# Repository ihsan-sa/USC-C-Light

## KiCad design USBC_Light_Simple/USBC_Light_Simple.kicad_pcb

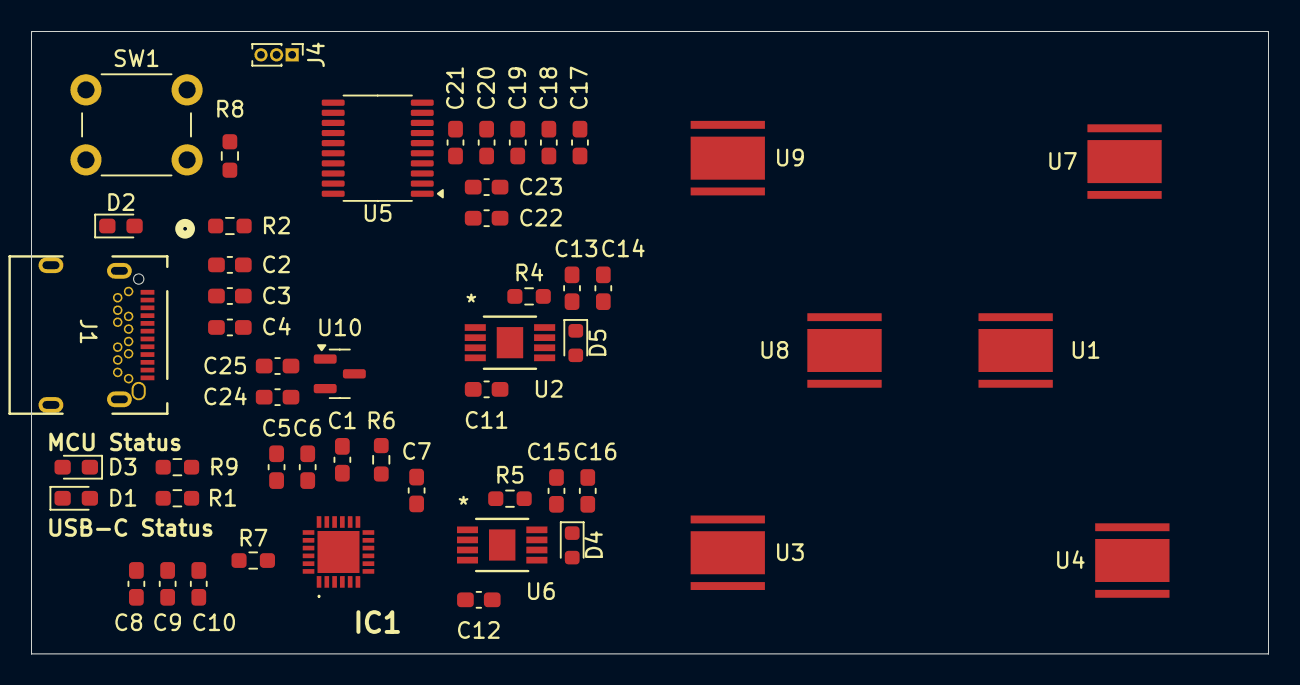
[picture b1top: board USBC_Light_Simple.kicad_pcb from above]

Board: 2 copper layers, 79.5 x 40.0 mm, 52 parts (0 on the bottom side), 36 nets, no tracks yet.

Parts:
C1, C4, C6, C7, C10, C11, C12, C13, C15, C19, C20, C25: 100n; C_0603_1608Metric_Pad1.08x0.95mm_HandSolder
C2, C8: 10u; C_0603_1608Metric_Pad1.08x0.95mm_HandSolder
C3, C5, C9, C14, C16, C17, C18, C24: 1u; C_0603_1608Metric_Pad1.08x0.95mm_HandSolder
C21: 10n; C_0603_1608Metric_Pad1.08x0.95mm_HandSolder
C22, C23: *; C_0603_1608Metric_Pad1.08x0.95mm_HandSolder
D1, D2, D3: LED; LED_0603_1608Metric_Pad1.05x0.95mm_HandSolder
D4, D5: D; D_0603_1608Metric
IC1: AP33772SDKZ-13-FA01; AP33772SDKZ13FA01
J1: USB_C_Receptacle; CONN24_4056-03-A_GCT
J4: Screw_Terminal_01x03; PinHeader_1x03_P1.00mm_Vertical
R1, R9: 1k; R_0603_1608Metric_Pad0.98x0.95mm_HandSolder
R2: 100k; R_0603_1608Metric_Pad0.98x0.95mm_HandSolder
R4, R5: RS; R_0603_1608Metric_Pad0.98x0.95mm_HandSolder
R6, R8: 10k; R_0603_1608Metric_Pad0.98x0.95mm_HandSolder
R7: 100; R_0603_1608Metric_Pad0.98x0.95mm_HandSolder
SW1: SW_Push; SW_PUSH_6mm
U1, U3, U4, U7, U8, U9: XHP50B-00-0000-0D0BJ440E; CHIP_D0BJ440E_WFS
U2, U6: AL8861MP-13; MSOP-8EP_DIO
U5: STM32C011F6Px; TSSOP-20_4.4x6.5mm_P0.65mm
U10: AP2127N-3.3; SOT-23

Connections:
+3V3: C17.1, C18.1, C19.1, C20.1, C21.1, C24.1, C25.1, R8.1, U5.4 (VDD), U10.2 (VO)
+5V: C5.1, C6.1, IC1.20 (V5V), U10.3 (VI)
+18V: C7.1, IC1.12 (V18)
/LEDs/LED_1: R4.2, U2.1 (ISENSE), U9.1
/LEDs/LED_2: R5.2, U1.1, U6.1 (ISENSE)
/LEDs/LX_1: D5.2 (A), U2.5 (LX), U2.6 (LX)
/LEDs/LX_2: D4.2 (A), U6.5 (LX), U6.6 (LX)
/LEDs/Thermal_Pad: U1.2, U3.2, U4.2, U7.2, U8.2, U9.2
/LEDs/VSET_1: C11.1, U2.4 (VSET)
/LEDs/VSET_2: C12.1, U6.4 (VSET)
/MCU/I2C_SCL: IC1.5 (SCL), U5.20 (PB6)
/MCU/I2C_SDA: IC1.4 (SDA), U5.1 (PB7)
/MCU/NRST: R8.2, SW1.2, U5.6 (PF2)
/MCU/OSC_IN: C22.2, U5.2 (PC14)
/MCU/OSC_OUT: C23.2, U5.3 (PC15)
/MCU/STATUS_LED: D3.2 (A), U5.11 (PA4)
/MCU/UART_RX: J4.3, U5.8 (PA1)
/MCU/UART_TX: J4.2, U5.7 (PA0)
/USB_C_IC/CC1: IC1.17 (CC1), J1.A5 (CC1)
/USB_C_IC/CC2: IC1.16 (CC2), J1.B5 (CC2)
/USB_C_IC/data_+: IC1.19 (DP), J1.A6 (D+), J1.B6 (D+)
/USB_C_IC/data_-: IC1.18 (DN), J1.A7 (D-), J1.B7 (D-)
GND: C1.2, C2.2, C3.2, C4.2, C5.2, C6.2, C7.2, C8.2, C9.2, C10.2, C11.2, C12.2, C13.2, C14.2, C15.2, C16.2, C17.2, C18.2, C19.2, C20.2, C21.2, C22.1, C23.1, C24.2, C25.2, D1.1 (K), D2.1 (K), IC1.3 (GND_1), IC1.25 (GND_2), J1.A1 (GND), J1.A12 (GND), J1.B1 (GND), J1.B12 (GND), J4.1, R6.2, R9.1, SW1.1, U2.2 (GND), U2.3 (GND), U5.5 (VSS), U6.2 (GND), U6.3 (GND), U10.1 (GND)
unnamed: D1.2 (A), R1.1
unnamed: D2.2 (A), R2.2
unnamed: D3.1 (K), R9.2
unnamed: C1.1, IC1.15 (IFB)
unnamed: IC1.8 (LED), R1.2
unnamed: IC1.13 (OTP), R6.1
unnamed: IC1.22 (VOUT), R7.2
unnamed: U1.3, U3.1
unnamed: U3.3, U4.1
unnamed: U7.1, U8.3
unnamed: U8.1, U9.3
VBUS: C2.1, C3.1, C4.1, IC1.1 (ISENP), J1.A4 (VBUS), J1.A9 (VBUS), J1.B4 (VBUS), J1.B9 (VBUS), R2.1
VLED: C8.1, C9.1, C10.1, C13.1, C14.1, C15.1, C16.1, D4.1 (K), D5.1 (K), R4.1, R5.1, R7.1, U2.8 (VIN), U6.8 (VIN)

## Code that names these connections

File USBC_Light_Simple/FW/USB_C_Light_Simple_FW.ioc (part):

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Mcu.Name=STM32C011F(4-6)Px
Mcu.Package=TSSOP20
Mcu.UserName=STM32C011F6Px
PA0.Mode=Asynchronous
PA0.Signal=USART1_TX
PA1.Mode=Asynchronous
PA1.Signal=USART1_RX
PA13.Mode=Serial_Wire
PA13.Signal=DEBUG_SWDIO
PA14-BOOT0.Mode=Serial_Wire
PA14-BOOT0.Signal=DEBUG_SWCLK
PA4.Signal=GPIO_Output
PB6.Mode=I2C
PB6.Signal=I2C1_SCL
PB7.Mode=I2C
PB7.Signal=I2C1_SDA
PC14-OSCX_IN\ (PC14).Mode=HSE-External-Oscillator-REMAPPED
PC14-OSCX_IN\ (PC14).Signal=RCC_OSCX_IN
PC15-OSCX_OUT\ (PC15).Mode=HSE-External-Oscillator-REMAPPED
PC15-OSCX_OUT\ (PC15).Signal=RCC_OSCX_OUT
RCC.HSE_VALUE=8000000
RCC.SYSCLKFreq_VALUE=12000000
board=custom

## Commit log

2025-07-13 init commit and added usb-c ic schematic
2025-07-14 Continued work:
    - Added LED driver and STM32
    - Began basic layout
2025-07-15 Fleshed out most of schematic. Now need to add component vals.
2025-07-17 Preliminary component placement on board.
